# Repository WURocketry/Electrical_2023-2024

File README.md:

# Electrical
Electrical / Software Development

* Circuit CAD
* Software

### Subteam Folders
Subteams are free to modify their own folder as they like - keep all your subteam related files/articles/figures within that folder.

### Subteam Branches
The "main" Electrical repository is organized into 2 subteam development branches:

* "dev/avionics"
* "dev/payload"
* "dev/airbrakes"

Subteam changes should be pushed and pull requests made only to the respective development subteam branch!

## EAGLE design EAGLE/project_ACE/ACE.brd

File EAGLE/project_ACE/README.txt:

Dependencies:
- ABX00042
- BNO08x .sch .brd
- OpenLog .sch .brd
- <TODO> Altitude 6 Click

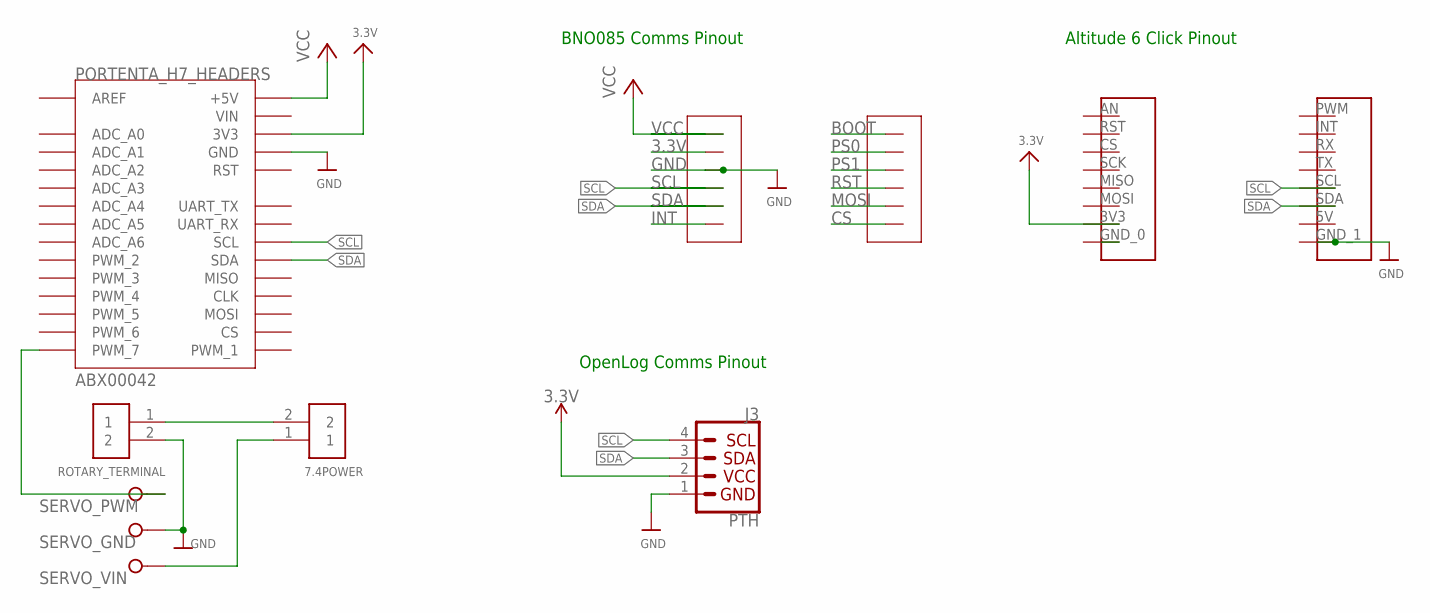
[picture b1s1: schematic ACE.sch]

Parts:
7.4POWER: 282837-2; TE_282837-2
J3: PTH; 1X04_NO_SILK
ROTARY_TERMINAL: 282837-2; TE_282837-2
SERVO: W237-3E
U$1: MIKROE-ALTITUDE-6-CLICK-DVC; MIKROE-ALTITUDE-6-CLICK-PINOUT
U$5: ADAFRUIT_BNO08X; ADAFRUIT_BNO08X_FOOTPRINT
U$10: ABX00042_HEADERS_IO; MODULE_ABX00042_HEADERS

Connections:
3.3V: J3.2 (VCC), U$1.3V3 (3.3V), U$10.J17 (3V3)
GND: J3.1 (GND), ROTARY_TERMINAL.2, SERVO.2, U$1.GND_1, U$5.GND, U$10.J18 (GND)
SCL: J3.4 (SCL), U$1.SCL, U$5.SCL, U$10.J22 (SCL)
SDA: J3.3 (SDA), U$1.SDA, U$5.SDA, U$10.J23 (SDA)
SERVO_GND: 7.4POWER.2, ROTARY_TERMINAL.1
SERVO_PWM: SERVO.1, U$10.J9 (PWM_7)
SERVO_VIN: 7.4POWER.1, SERVO.3
VCC: U$5.VIN (VCC), U$10.J15 (+5V)

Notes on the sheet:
OpenLog Comms Pinout
BNO085 Comms Pinout
Altitude 6 Click Pinout

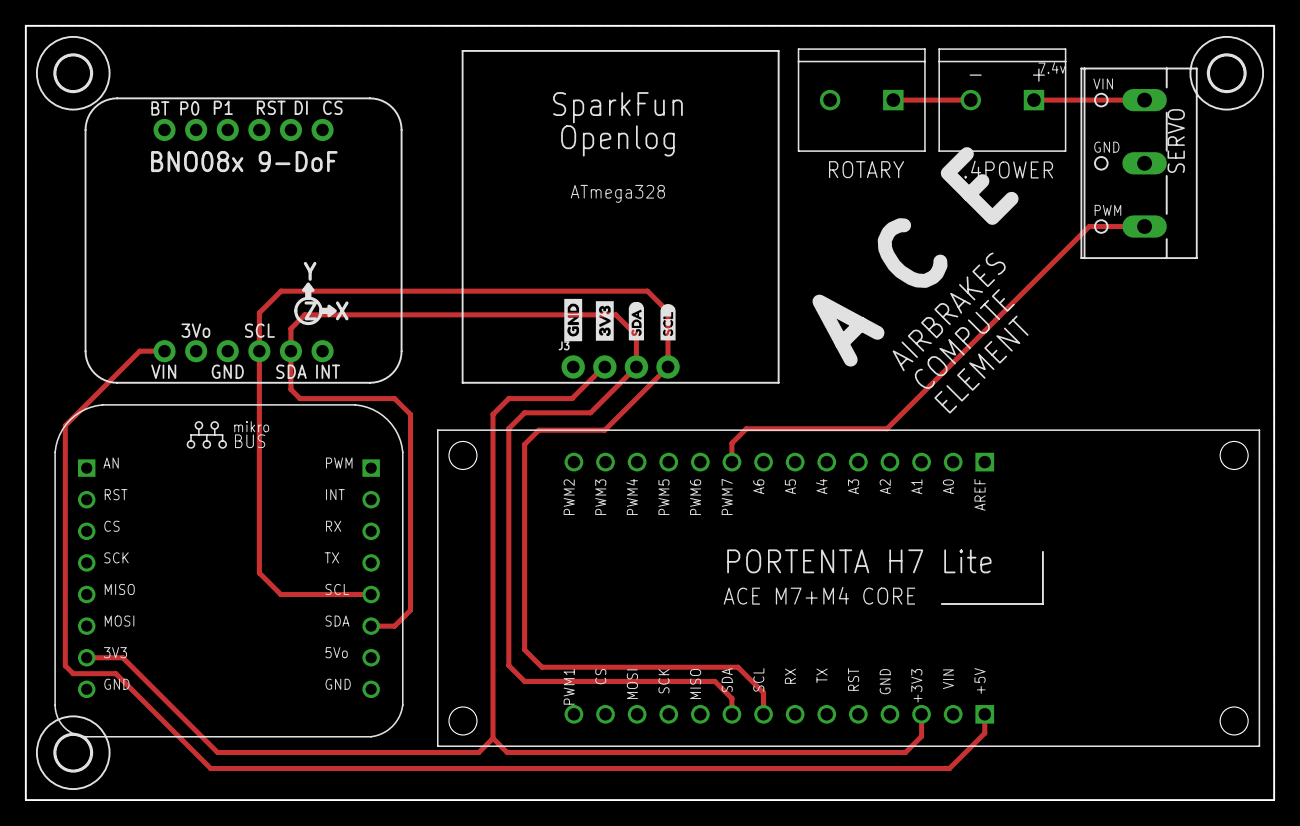
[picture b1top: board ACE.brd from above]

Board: 2 copper layers, 100.3 x 62.2 mm, 14 parts (0 on the bottom side), 8 nets.

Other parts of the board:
U$8: 3V3-03
U$9: GND-03
U$13, U$14, U$15: 2,8
U$16: SDA1
U$19: SCL2

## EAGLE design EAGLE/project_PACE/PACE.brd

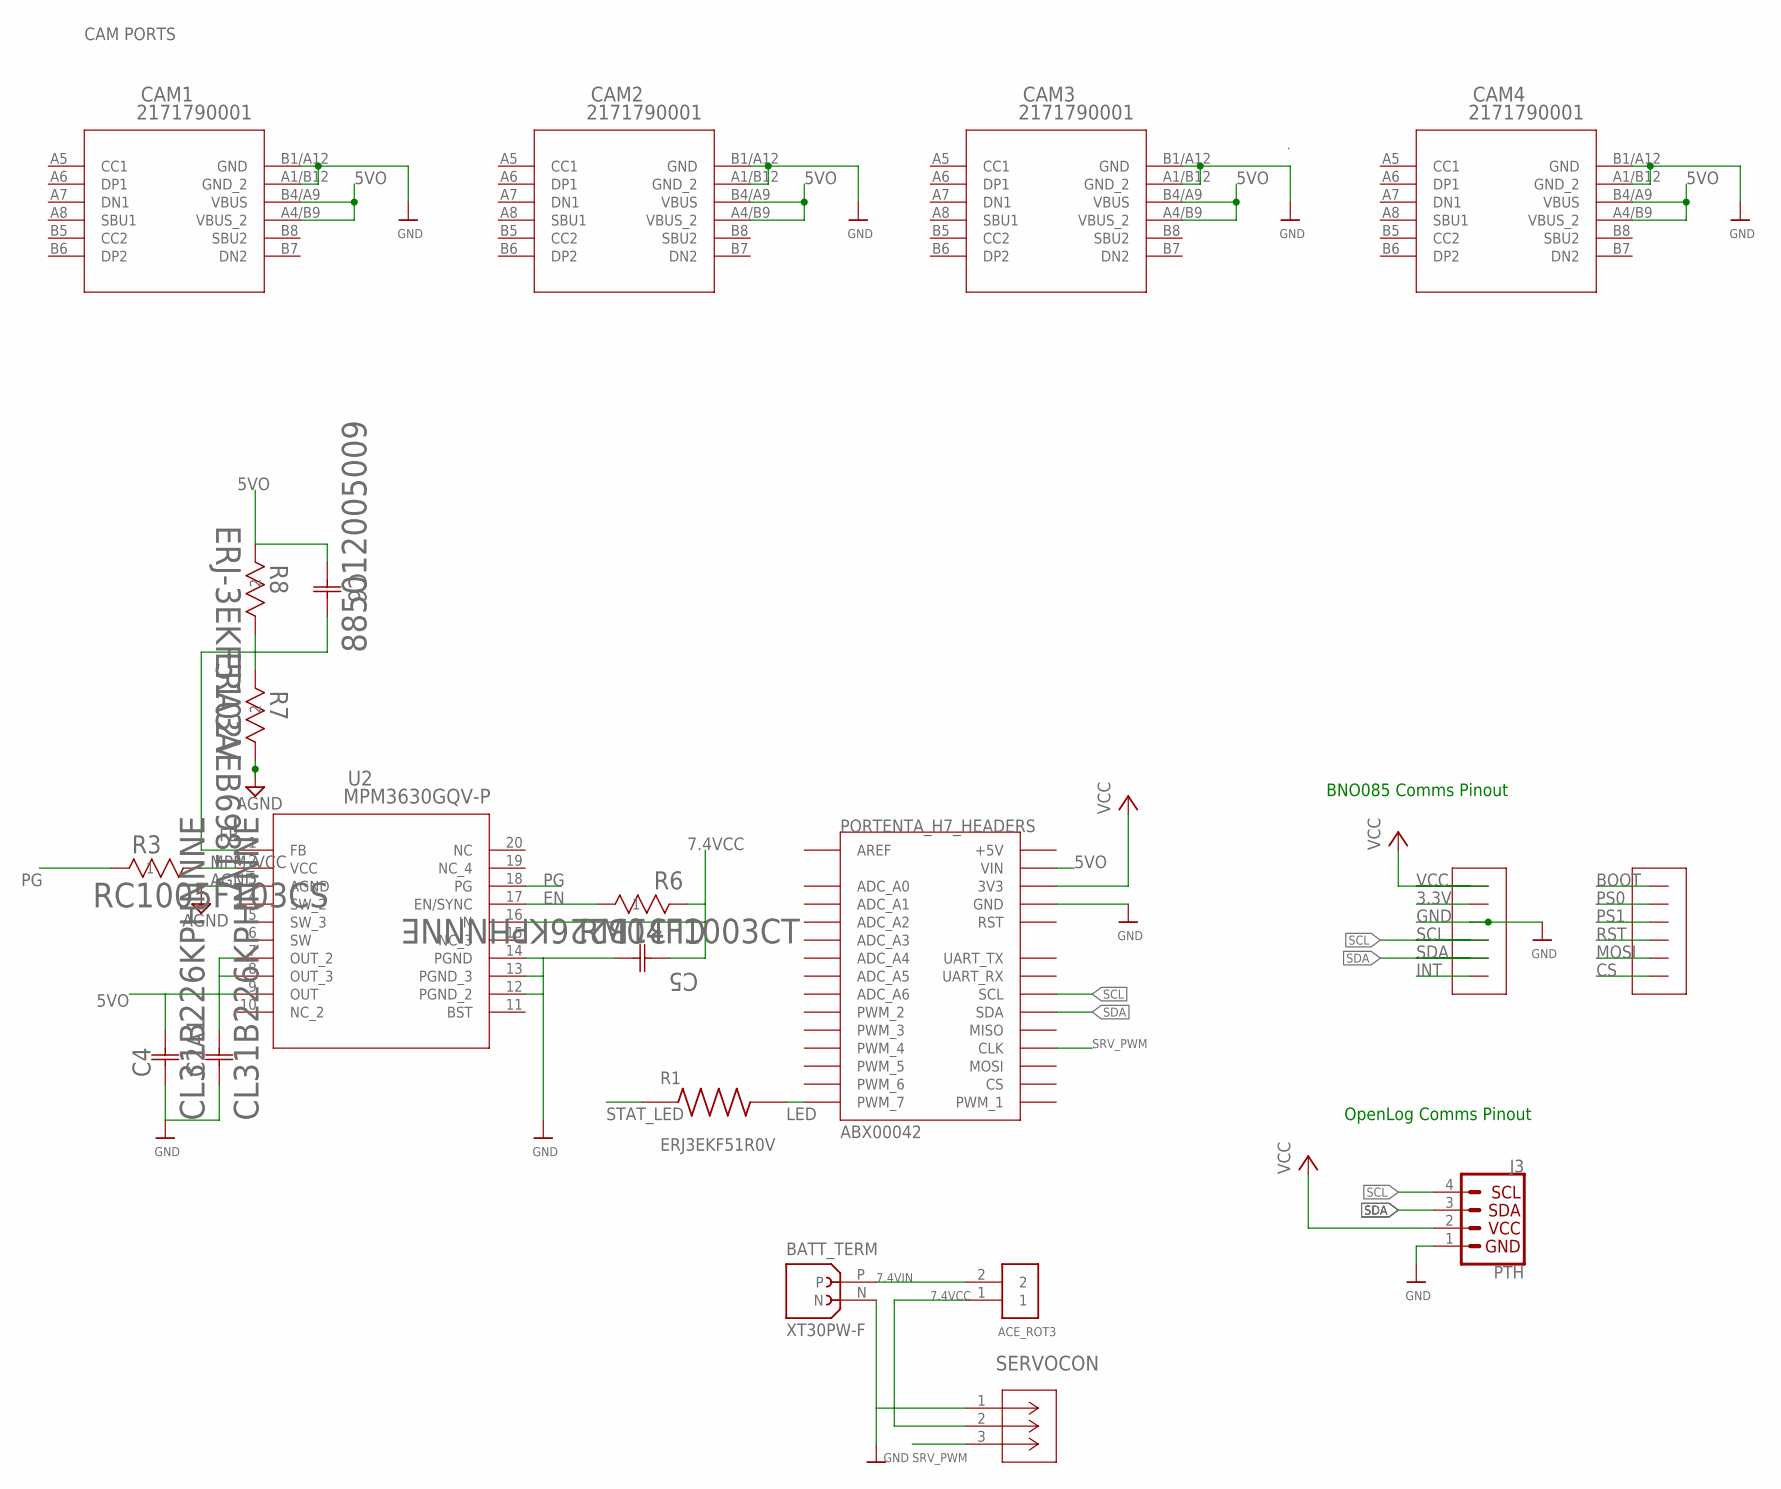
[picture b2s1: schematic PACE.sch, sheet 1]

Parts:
ACE_ROT3: 282837-2; TE_282837-2
BATT_TERM: XT30PW-F; AMASS_XT30PW-F
C2A1, C4, C5: CL31B226KPHNNNE; CAP_CL31_SAM
C6: 885012005009; CAP_885012005_WRE
CAM1, CAM2, CAM3, CAM4: 2171790001; 2171790001_MOL
J3: PTH; 1X04_NO_SILK
R1: ERJ3EKF51R0V; RES_ERJ3EKF51R0V
R3: RC1005F103CS; RES_1005_SAM
R6: RM04F1003CT; RES_RM04_CCE
R7: ERA3AEB6981V; RES_ERA3A_0603_PAN
R8: ERJ-3EKF5102V; RC0603N_PAN
SERVOCON: B03B-PASK-1_(LF)_(SN); CONN_B03B-PASK-1_(LF)_(SN)_JST
U2: MPM3630GQV-P; QFN3P0X5P0X1P6_MPM3630_MNP
U$5: ADAFRUIT_BNO08X; ADAFRUIT_BNO08X_FOOTPRINT
U$10: ABX00042_HEADERS_IO; MODULE_ABX00042_HEADERS

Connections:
5VO: C2A1.2, C4.2, C6.2, CAM1.A4/B9 (VBUS_2), CAM1.B4/A9 (VBUS), CAM2.A4/B9 (VBUS_2), CAM2.B4/A9 (VBUS), CAM3.A4/B9 (VBUS_2), CAM3.B4/A9 (VBUS), CAM4.A4/B9 (VBUS_2), CAM4.B4/A9 (VBUS), R8.2, U2.7 (OUT_2), U2.8 (OUT_3), U2.9 (OUT), U$10.J16 (VIN)
7.4VCC: ACE_ROT3.1, C5.1, R6.2, SERVOCON.2, U2.16 (IN)
7.4VIN: ACE_ROT3.2, BATT_TERM.P
AGND: R7.1, U2.3 (AGND)
EN: R6.1, U2.17 (EN/SYNC)
FB: C6.1, R7.2, R8.1, U2.1 (FB)
GND: BATT_TERM.N, C2A1.1, C4.1, C5.2, CAM1.A1/B12 (GND_2), CAM1.B1/A12 (GND), CAM2.A1/B12 (GND_2), CAM2.B1/A12 (GND), CAM3.A1/B12 (GND_2), CAM3.B1/A12 (GND), CAM4.A1/B12 (GND_2), CAM4.B1/A12 (GND), J3.1 (GND), SERVOCON.1, U2.12 (PGND_2), U2.13 (PGND_3), U2.14 (PGND), U$5.GND, U$10.J18 (GND); also elsewhere on the board
LED: R1.2, U$10.J9 (PWM_7)
MPM_VCC: R3.2, U2.2 (VCC)
PG: R3.1, U2.18 (PG)
SCL: J3.4 (SCL), U$5.SCL, U$10.J22 (SCL); also elsewhere on the board
SDA: J3.3 (SDA), U$5.SDA, U$10.J23 (SDA); also elsewhere on the board
SRV_PWM: SERVOCON.3, U$10.J25 (CLK)
STAT_LED: R1.1
VCC: J3.2 (VCC), U$5.VIN (VCC), U$10.J17 (3V3); also elsewhere on the board

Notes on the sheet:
OpenLog Comms Pinout
BNO085 Comms Pinout
CAM PORTS

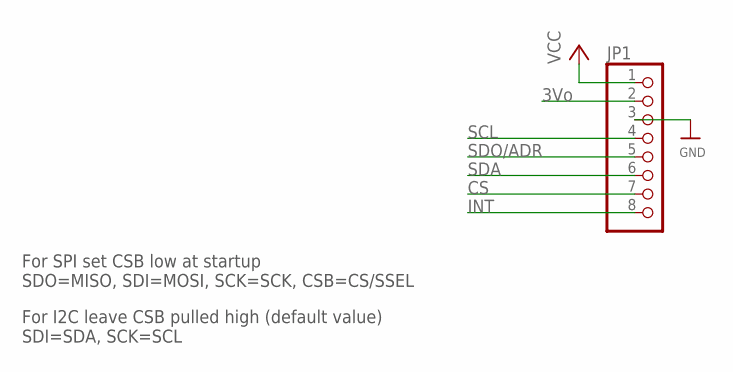
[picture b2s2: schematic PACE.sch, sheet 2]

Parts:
JP1: HEADER-1X870MIL; 1X08_ROUND_70

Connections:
CS: JP1.7
GND: JP1.3; also elsewhere on the board
INT: JP1.8
SCL: JP1.4; also elsewhere on the board
SDA: JP1.6; also elsewhere on the board
SDO/ADR: JP1.5
VCC: JP1.1; also elsewhere on the board

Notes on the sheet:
For SPI set CSB low at startup SDO=MISO, SDI=MOSI, SCK=SCK, CSB=CS/SSEL
For I2C leave CSB pulled high (default value) SDI=SDA, SCK=SCL
3Vo

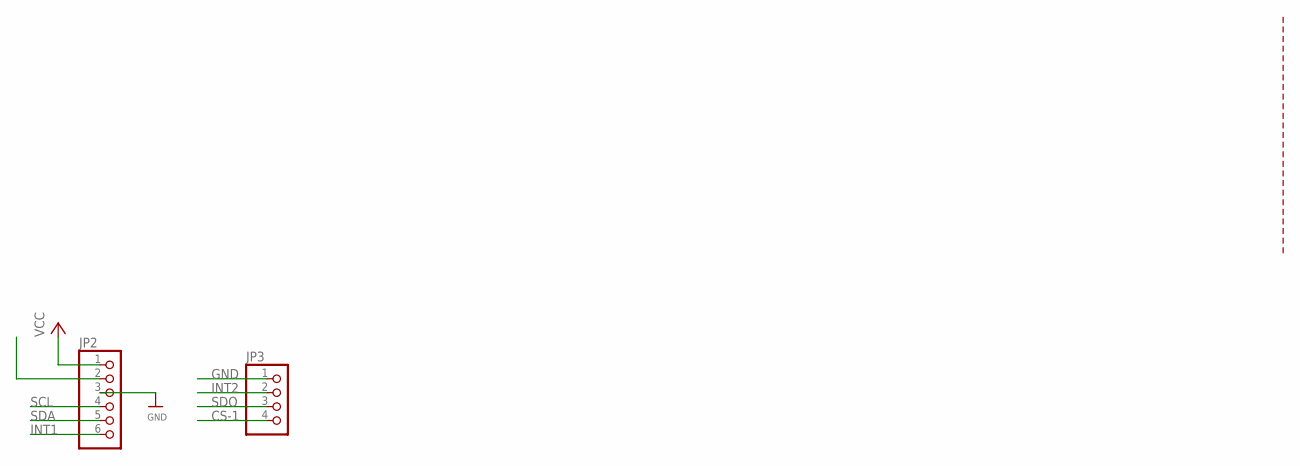
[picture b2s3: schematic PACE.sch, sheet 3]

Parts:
JP2: HEADER-1X670MIL; 1X06_ROUND_70
JP3: HEADER-1X4ROUND; 1X04_ROUND

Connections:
CS-1: JP3.4
GND: JP2.3, JP3.1; also elsewhere on the board
INT1: JP2.6
INT2: JP3.2
SCL: JP2.4; also elsewhere on the board
SDA: JP2.5; also elsewhere on the board
SDO: JP3.3
VCC: JP2.1; also elsewhere on the board

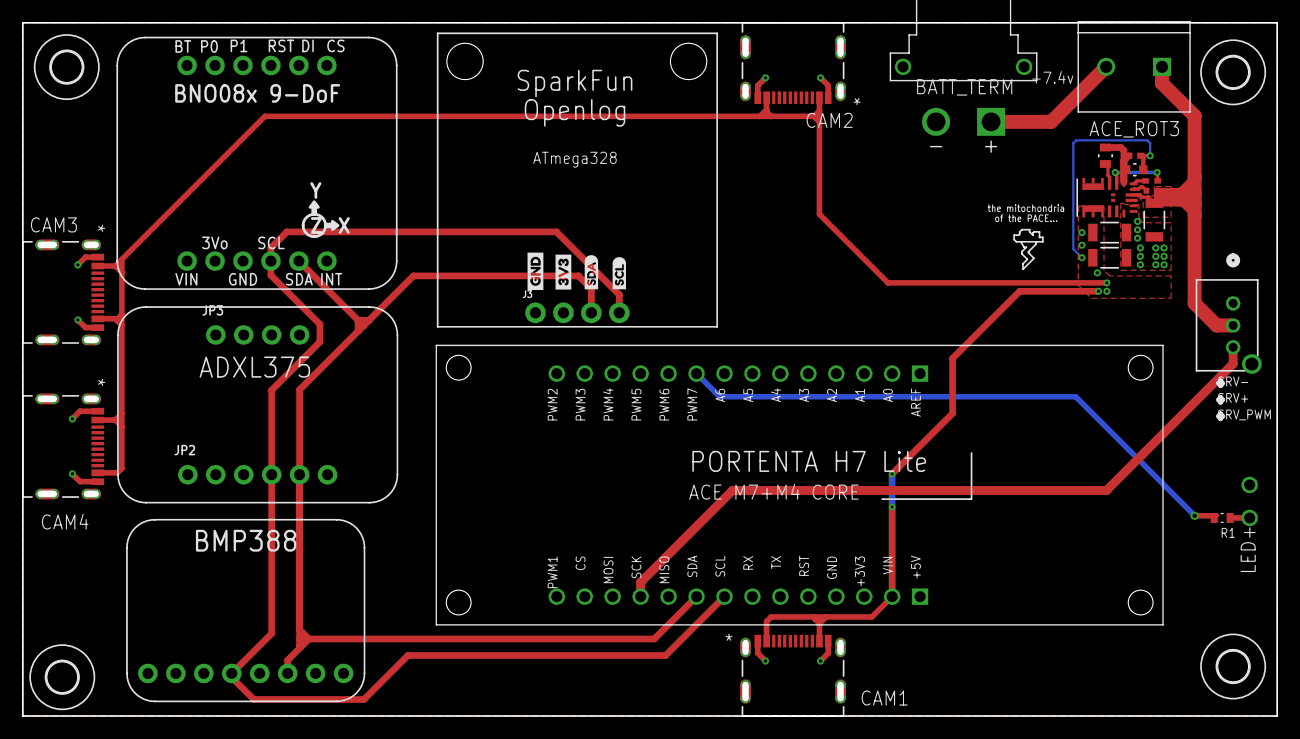
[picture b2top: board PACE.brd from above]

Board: 2 copper layers, 113.5 x 62.5 mm, 33 parts (0 on the bottom side), 14 nets.

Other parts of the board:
JP4, JP5: STAND-OFF
U$8: 3V3-03
U$9: GND-03
U$13, U$14, U$15, U$29: 2,8
U$16: SDA1
U$19: SCL2

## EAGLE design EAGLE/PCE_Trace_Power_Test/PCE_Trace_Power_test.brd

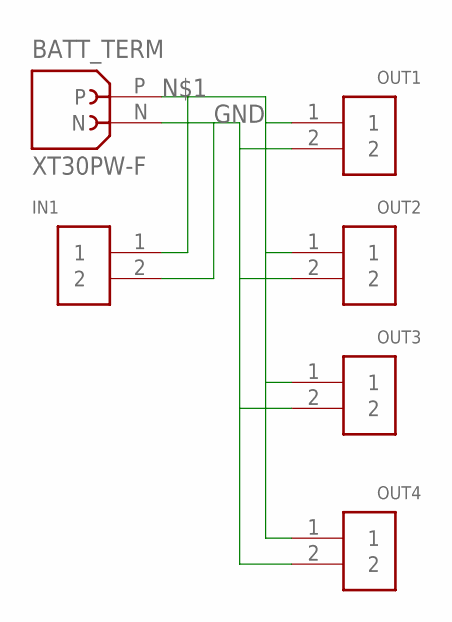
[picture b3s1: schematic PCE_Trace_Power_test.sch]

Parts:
BATT_TERM: XT30PW-F; AMASS_XT30PW-F
IN1: 282837-2; TE_282837-2
OUT1, OUT2, OUT3, OUT4: 282837-2; TE_282837-2

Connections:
GND: BATT_TERM.N, IN1.2, OUT1.2, OUT2.2, OUT3.2, OUT4.2
unnamed: BATT_TERM.P, IN1.1, OUT1.1, OUT2.1, OUT3.1, OUT4.1

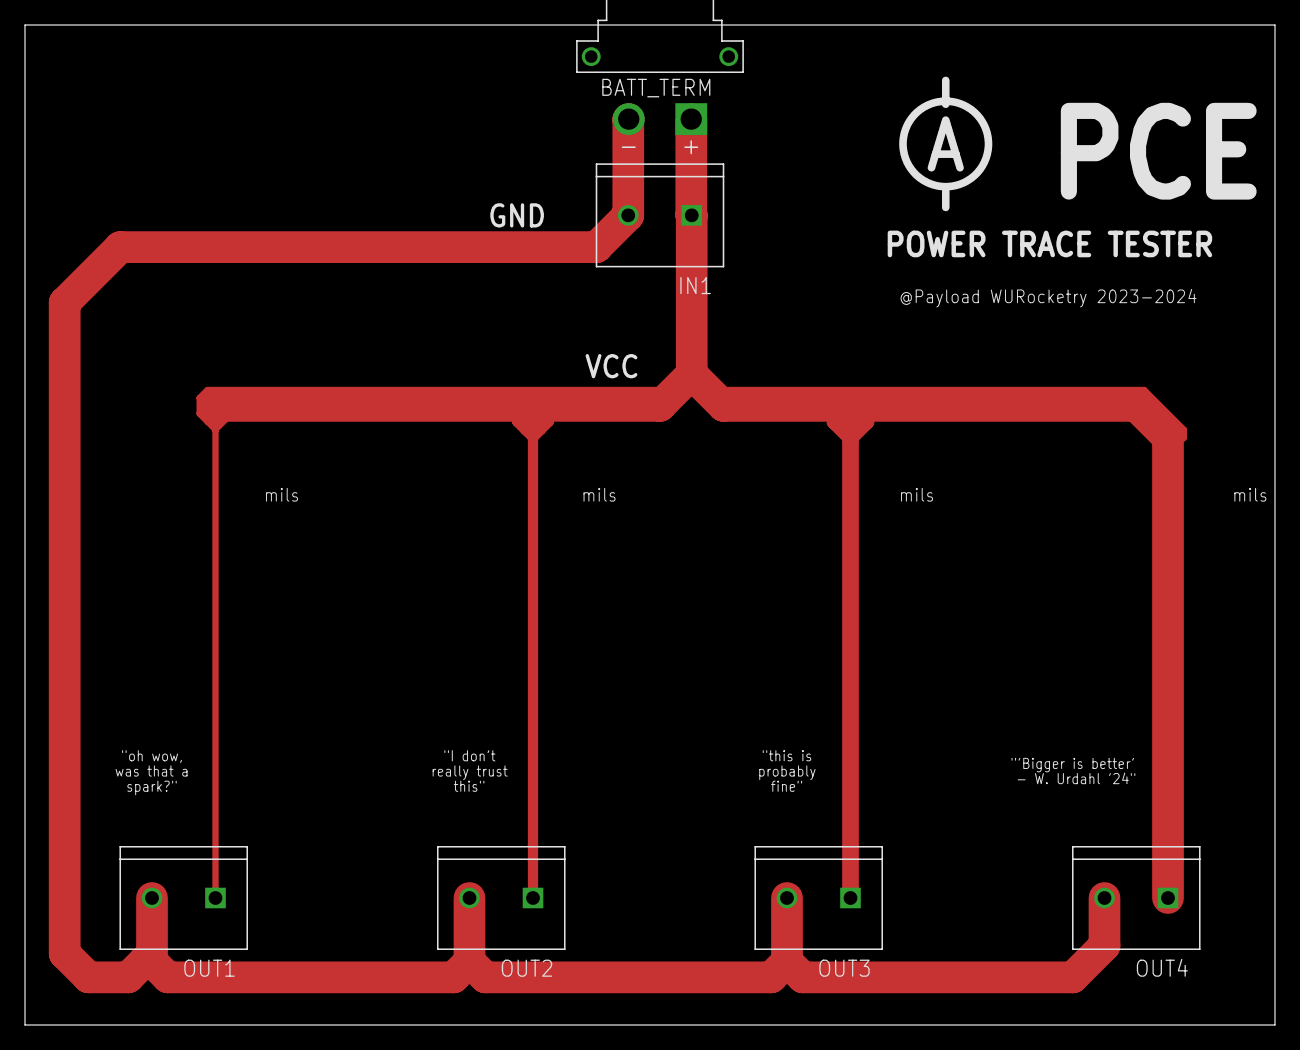
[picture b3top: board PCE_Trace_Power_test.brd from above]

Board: 2 copper layers, 100.0 x 80.0 mm, 6 parts (0 on the bottom side), 2 nets.

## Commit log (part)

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2023-10-22 Fixed delta timing from comments
2023-10-22 base station script
2023-10-22 Update main.cpp
    Updated standby state
2023-10-22 Initial FSM integration for ACE (#47)
    * Update main.cpp
    Implemented FSM transitions
    * Update main.cpp
    Updated standby state
    ---------
2023-10-23 Create vlt.h
    Creates velocity look-up table for Full Scale as header file
2023-10-24 move vlt table
2023-10-24 fixing merge conflicts
2023-10-25 Modified delta timing and changed time status to unsigned long
2023-10-25 Add BAD approximations for mass change over time and drag dependence on Vel
2023-10-25 Make delta timing discrete and replace COMPUTE poll condition
    * Last time variables are incremented by respective delta times
    * COMPUTE runs at multiples of 4 SAMPLE polls
2023-10-25 Delta timing for components (#46)
    * Fixed delta timing from comments
    * Fixed delta timing, no compiler errors
    * Modified delta timing and changed time status to unsigned long
    ---------
2023-10-29 adding neopixel stuff, compiles
2023-10-29 Revert "Payload/small csv"
2023-11-01 FlightMonitor header file
2023-11-01 LinearInterp attempt
2023-11-01 PID Control/Servo Test Control File
2023-11-01 Update main.ino (#54)
    * Update main.ino
    * Update main.ino
2023-11-02 Add simulation OR data sample
2023-11-02 Add necessary files and definitions
2023-11-03 Add necessary files and definitions (#57)
2023-11-03 Add simulation OR data sample (#56)
    * Add simulation OR data sample
    * Handle negative simulation time exception case
    ---------
2023-11-03 Implement all state transtions
2023-11-03 Create Persistences
    landing transition does not behave as expected.
2023-11-04 Fix Bounds
2023-11-04 hello world on receiving end and server end both work
2023-11-04 Change persistence and remove include
2023-11-04 Added not about removing wait for serial connection for flight
2023-11-04 Attempt at preprocessor stuff
    Also added something to .ini to make the sdram.h work... it did not
2023-11-05 Implement all state transitions (#58)
    * Implement all state transtions
    * Create Persistences
    landing transition does not behave as expected.
    * Move Evaluation of Flight Monitor
    * Fix Bounds
    * create ringBuffer for data storage
2023-11-05 bme680 delta timing test
2023-11-05 Draft PID header file
2023-11-06 Added linear interp
2023-11-08 Update PID header file
2023-11-08 state vector API work
2023-11-08 new radio integration
2023-11-09 add IMU platformIO port
2023-11-09 Fix SDRAM init and test successful physical build
2023-11-09 Added servo library
2023-11-10 Review PID controller
2023-11-10 Implement PID controller into ACE
2023-11-10 Draft PID header file (#61)
    * Draft PID header file
    * Update PID header file
    * Prototype of PID_controller class
    * changed error
    * Added servo library
    * Review PID controller
2023-11-10 allow code to work on RP2040
2023-11-10 encapsulate kalman stuff into header file
    I re-activated the simulation BTW
2023-11-10 small fixes
2023-11-10 Integrated BNO085
2023-11-11 update VLT
2023-11-11 update Simulation
2023-11-11 add quaternions
2023-11-11 ALtitude readings
2023-11-11 Collect sensor data
2023-11-11 sync analysis files
2023-11-11 Implement measurement structs
2023-11-11 Update sample (IMU/Alt) frequency (100Hz) and compute frequency (100Hz)
2023-11-11 Create accel Replace
2023-11-11 add acceleration Replacement
2023-11-11 Change SDRAM size to record 5 minutes of flight
2023-11-11 Remove additional variables (for now)
2023-11-11 PID fix investigation
2023-11-12 Clean up FlightMon and kalman defines
2023-11-12 Fix flight monitor init
2023-11-12 PID fixes
2023-11-12 Servo control only in control phase
2023-11-12 First flight-ready prototype build
2023-11-15 Added rp2040 support
2023-11-15 time testing
2023-11-15 Revert "added new array"
    This reverts commit a46a1262b01a06a3490d61831517f0d6ea0d2fea.
    dd
2023-11-15 Revert "Revert "added new array""
    This reverts commit e6800fba9e1aacb9877302714bf646f0352c25b9.
    dfdsf
2023-11-15 Fix rotation vector for inertial frame
2023-11-19 delta timing test
2023-11-19 test
2023-11-19 Autumn's Updates + Main Fixes
2023-11-19 stateVec api functions
2023-11-19 make i2c run faster
2023-11-29 Temp comment Wire crash fix
2023-12-08 added servo library import statement
2023-12-08 Hmm, maybe this servo stuff will work
2023-12-09 changed control line at end to use new servo step function instead of writing direct to servo
2023-12-09 Made most changes that Brendan requested.
2023-12-10 Finalize v0.2 ACE PCB
2023-12-14 Add CAM job for ACEv0.2
2023-12-14 Minor reformatting
2023-12-14 Payload/asynchronus bme (#68)
    * BME Asynchronus Reading
    * bme680 delta timing test
    * delta timing test
    * test
    ---------
2023-12-14 Add pre-flight configuration
2023-12-14 Reorganization for linkage order and static storage
2023-12-15 Restructure airbrakes code directories
2023-12-15 Refactor FSM definitions into namespace
2023-12-15 Refactor measurement code and simplify sensor sample includes
2023-12-15 initial investigation
2023-12-16 Add initialization checks
2023-12-16 Implement Adafruit ADXL345 sensor
2023-12-17 Fix BMP388 calibration didInit bug
2023-12-17 Modify sensor integration and support ADXL345 linear acceleration measurement
2023-12-17 Update OpenLogger class instance and fix init
2023-12-17 Move OpenLog into component class (#84)
    * Move openlog into component class
    * Add initialization checks
    * Update OpenLogger class instance and fix init
    ---------
2023-12-17 Fix FlightMonitor pass-by-value copy bug
2023-12-17 Airbrakes/investigate fm update (#85)
    * initial investigation
    * Fix FlightMonitor pass-by-value copy bug
2023-12-17 Add servo actuation init check
2023-12-17 Invert servo angle control and add development mode prints/sim
2023-12-17 Flight changes
2023-12-18 Subscale launch changes and servo range tweaks
2024-01-12 Create stale.yml test (#89)
    Testing gh actions
2024-01-12 Update pio-build-airbrakes.yml
    Point all run working directories to Pio root by default
2024-01-12 Merge test GH Actions (#91)
    * Create stale.yml test
    Testing gh actions
    * Create pio-build-airbrakes.yml
    PlatformIO build workflow for Airbrakes
    * Update pio-build-airbrakes.yml
    Point all run working directories to Pio root by default
2024-01-12 Move .github/workflows/pio-build-airbrakes.yml to dev/airbrakes
    Deleting file to move to correct workflow branch
2024-01-12 Add pio build workflow
2024-01-12 aaand move directory because I am blind
2024-01-14 Update pio-build.yml
    Modify for PR trigger
2024-01-14 Sync pio-build.yml
    From dev/airbrakes
2024-01-14 Sync auto-assign.yml
    from main
2024-01-14 Add mock file
2024-01-14 Mock updates with changes
2024-01-14 Sync pio-build.yml
    from main
2024-01-14 Update pio-build.yml
    Add gh_token for CLI access
2024-01-14 Update pio-build.yml
    Check relevant changes after github checkout
2024-01-14 Update pio-build.yml
    Fix gh token and git diff
2024-01-14 Yet another test of irrelevant change
2024-01-14 testing again, irrelevant change
2024-01-14 now, making a relevant change in the relevant directory...
2024-01-14 another relevant change
2024-01-14 Update pio-build.yml
    Fix dorny filter
2024-01-14 changed
2024-01-14 test push with faulty code
2024-01-19 Add Unified Sensor lib
2024-01-19 fixes
2024-01-19 updating platformio
2024-01-20 platformio bugfixing
2024-01-20 Fix EEPROM include and successful target compilation
2024-01-27 Added tilt detection
2024-01-28 Reorganize file structure
2024-01-30 Test payload
2024-01-30 update with change filter
2024-01-30 Test pio build in project
2024-01-30 removed file in test pio path
2024-01-30 Add gh action workflows
2024-02-04 servo class changes
2024-02-07 Added tilt fault protection and stow method
2024-02-08 Added standby transition to FSM
2024-02-09 trying to fix gps
2024-02-09 Add servo updates during controlStandby state
2024-02-10 Minor degree offset config for aft assembly
2024-02-10 FS VLT
2024-02-11 trim data that transmit live
2024-02-13 PACE Start
2024-02-13 New mavlink python script added
2024-02-14 First draft of PACE
2024-02-14 Add MPM3630 block
2024-02-14 Add 51 Ohm resistor part
2024-02-15 added base station code
2024-02-18 fixed bug
2024-02-19 Reorganize local EAGLE files
2024-02-19 Reorganize PACE to new project folder
2024-02-19 Move EAGLE into subteam independent folder
2024-02-19 Add PCE trace width test EAGLE
2024-02-25 Move ACE complete message into loop
2024-02-25 Add forced extension and status led options
2024-02-26 Fix dimensions
2024-02-27 Update USB-C with Molex mfg part
2024-03-08 fix_datalog
2024-03-09 attempt
2024-03-21 Create LOGGING_TEST.ino
    openlog test
2024-03-21 initial script update
2024-03-21 updated error handling
2024-03-22 abbys files
2024-03-22 control flow refining
2024-03-22 base station transmit from avionics/nasir
2024-03-22 change the reconnection sequence
2024-03-23 Update main.ino
    shifted .append() call in logData and removed .appen() call in setup
2024-03-23 changed port
2024-03-23 launch day telemetry
2024-03-24 LOGGING_TEST
    fixed logging test
2024-03-24 Cleaning the code
2024-03-25 Modifications from Sunday's test
2024-03-26 drone control modifications
2024-03-28 adding the new life metrics code
2024-03-28 added neoPixel code to life_metrics_reborn
2024-03-28 python script runs on boot and drone connection error handling works
2024-03-28 Add code to pull mosfet gates to low on startup
2024-03-28 to clean status log file
2024-03-29 miscellaneous during testing
2024-03-29 changing
2024-03-29 Rename rc.local to rc.local_code
2024-03-29 updated alaunch day receive
2024-03-31 deleted !serial line
2024-04-04 changes to init order
2024-04-04 updated packet status enum
2024-04-04 documentation
2024-04-04 copypasta from Adafruit ADXL345
2024-04-05 accelorometer work
2024-04-06 rewrote error led a bit
2024-04-07 Clarify error decay function
2024-04-10 nothing?
2024-04-13 updating baseline for spg
2024-04-13 Radio calculation
2024-04-21 VLT investigation
2024-04-21 Document Kalman.h
2024-04-21 Fix library dependencies
2024-04-21 ACE 3.0
2024-04-21 Velocity Look-up table work
2024-04-22 make slight changes to ACE 3.0
2024-04-23 fix some labelling on schematic for ACE 3.0
2024-04-24 Project documentation + READMEs
2024-04-24 Document EAGLE/
2024-05-03 Beginning refactor + add local libraries folder
2024-05-04 sd card interfacing
2024-05-04 Update traces
2024-05-05 Redraw left power plane
2024-05-05 Test pour again
2024-05-05 loose wire test
2024-05-05 changed cs_sd to pull-up and fixed csb
2024-05-05 refilled pcb
2024-05-05 WIP wiring + DRC checks
2024-05-05 Fix gnd connection
2024-05-06 New Sensor Board - No pringles
2024-05-06 Kicad prototype/sd card (#110)
    * sd card interfacing
    * updated traces
    * Update traces
    * Updated traces
    * Redraw left power plane
    * Update RP2040_minimal_r2.kicad_pcb
2024-05-06 deleted everything (aka moved files around)
2024-05-06 make traces larger for PWR and GND
2024-05-06 Fix DRC unconnections
2024-05-06 Update Symbol for edge connector
2024-05-06 RP2040 Daughter Board
2024-05-06 Update .gitignore + rm cache file
2024-05-06 Final routing draft + DRC fixes
2024-05-06 Silkscreen
2024-05-06 DRC warning fixes
2024-05-06 Update footprint refs
2024-05-07 Final review + DRC pass
2024-05-07 make edge connected .2 mm smaller
2024-05-07 silkscreens
2024-05-07 Finalize KiCad prototype of ACE 3.0 (#111)
    * Beginning refactor + add local libraries folder
    * Kicad prototype/sd card (#110)
    * sd card interfacing
    * updated traces
    * Update traces
    * Updated traces
2024-05-07 Merge dev/airbrakes to 2023-2024 Electrical (#106)
    * init Airbrakes folder
    * Added data and barebones simulation
    * Update README.md
    * LaunchAndControlSim
    * update controller with drag VLT and integral term
    * change errorDecay to be dependent on altitude

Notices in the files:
parts and their libraries:
microbuilder: This work is placed in the public domain, and may be freely used for commercial and non-commercial work with the following conditions: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
SparkFun-PowerSymbols: Licensing: Creative Commons ShareAlike 4.0 International - https://creativecommons.org/licenses/by-sa/4.0
